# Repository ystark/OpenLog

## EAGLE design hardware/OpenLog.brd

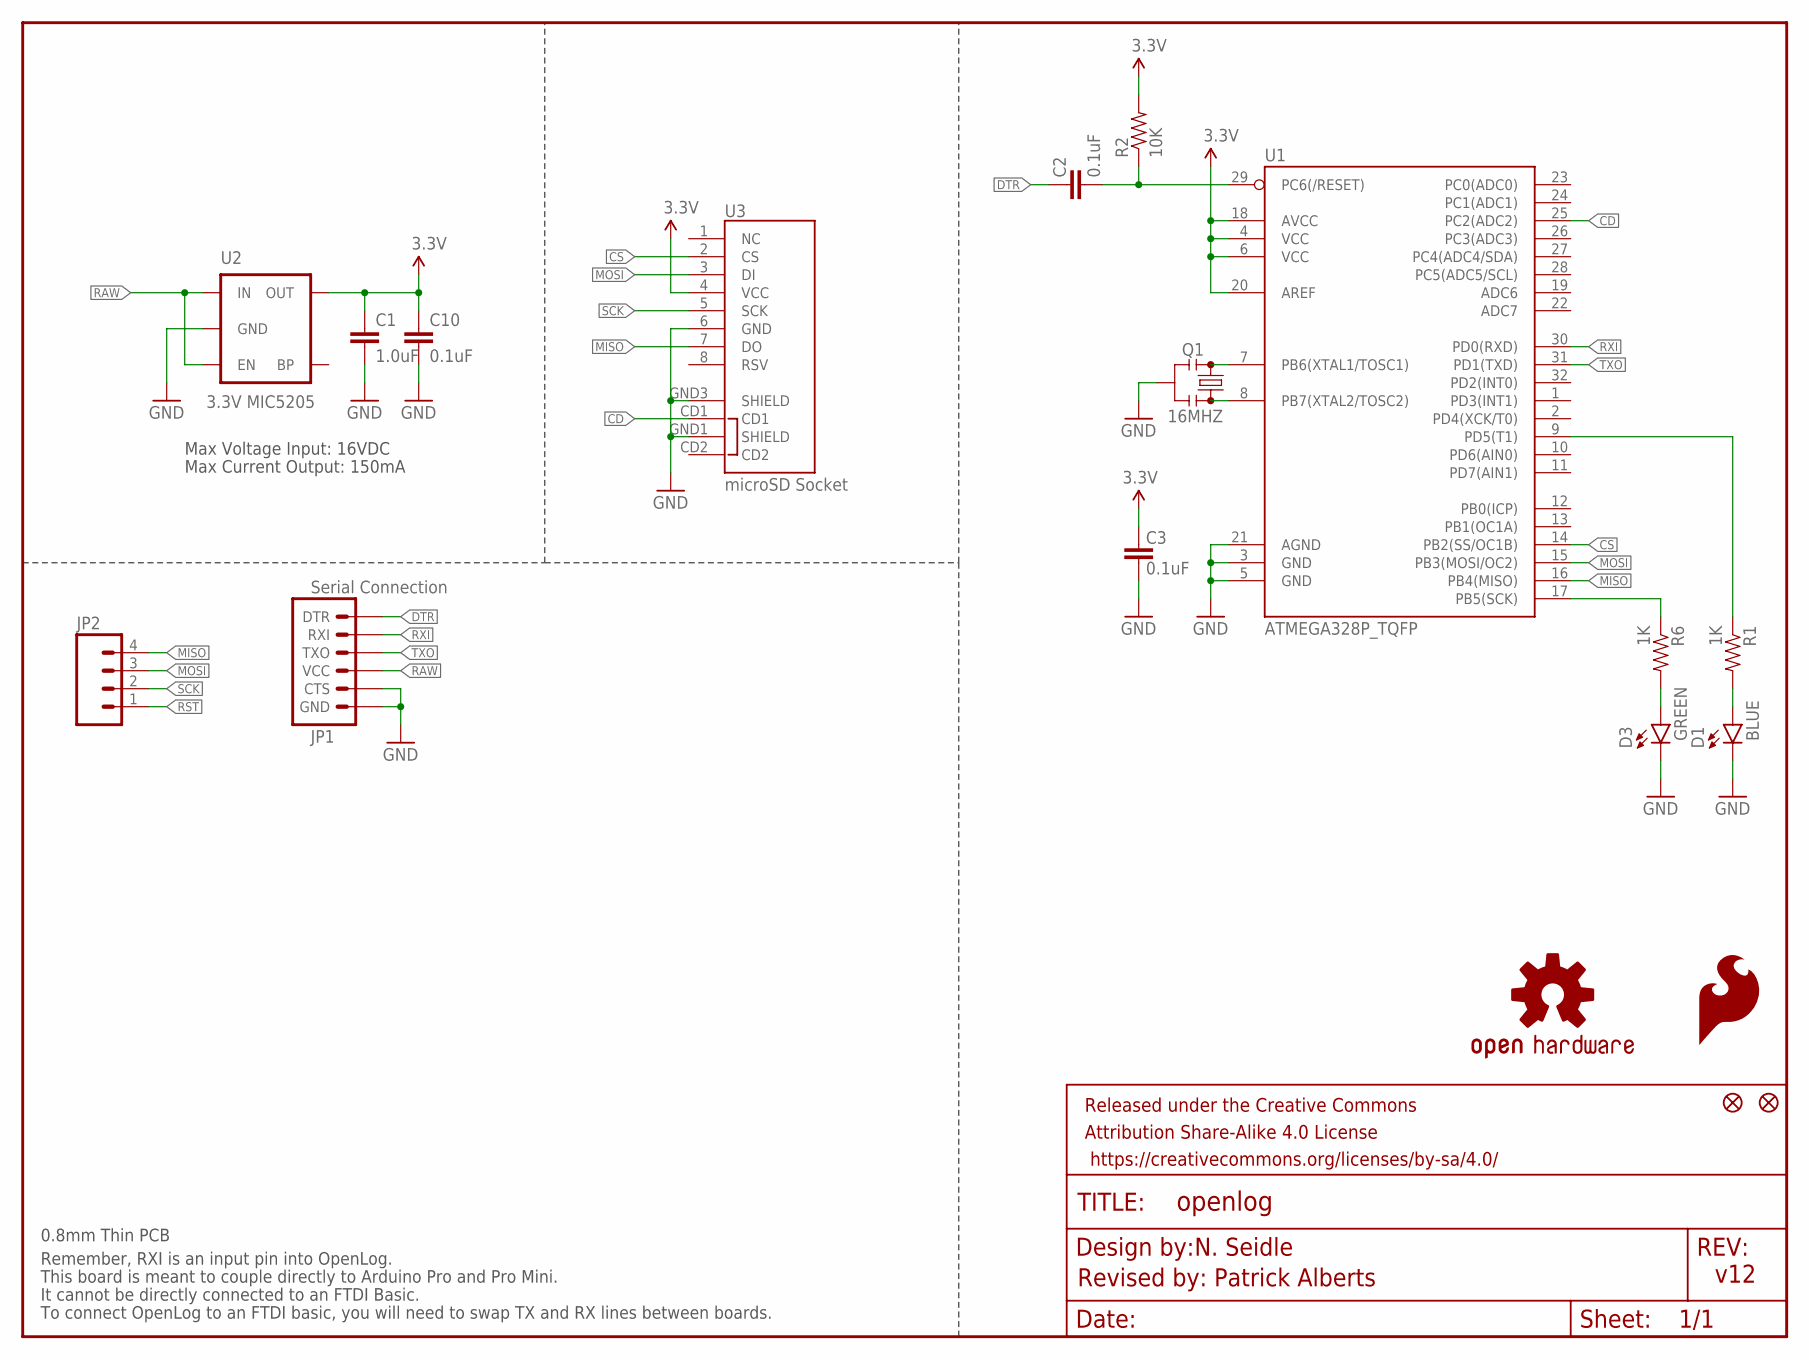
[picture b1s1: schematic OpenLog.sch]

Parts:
C1: 1.0uF; 0603-CAP
C2, C3, C10: 0.1uF; 0603-CAP
D1: BLUE; LED-0603
D3: GREEN; LED-0603
FID1, FID2: FIDUCIALUFIDUCIAL; MICRO-FIDUCIAL
FRAME1: FRAME-LETTER; CREATIVE_COMMONS
JP1: Serial Connection; 1X06
JP2: M04PTH; 1X04
LOGO1: SFE_LOGO_FLAME.1_INCH; SFE_LOGO_FLAME_.1
LOGO2: OSHW-LOGOS; OSHW-LOGO-S
Q1: 16MHZ; RESONATOR-SMD
R1, R6: 1K; 0603-RES
R2: 10K; 0603-RES
U1: ATMEGA328P_TQFP; TQFP32-08
U2: 3.3V MIC5205; SOT23-5
U3: microSD Socket; MICROSD_1:1

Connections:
3.3V: C1.1, C3.2, C10.1, R2.2, U1.4 (VCC), U1.6 (VCC), U1.18 (AVCC), U1.20 (AREF), U2.5 (OUT), U3.4 (VCC)
CD: U1.25 (PC2(ADC2)), U3.CD1
CS: U1.14 (PB2(SS/OC1B)), U3.2 (CS)
DTR: C2.2, JP1.1 (DTR)
GND: C1.2, C3.1, C10.2, D1.C, D3.C, JP1.5 (CTS), JP1.6 (GND), Q1.2, U1.3 (GND), U1.5 (GND), U1.21 (AGND), U2.2 (GND), U3.6 (GND), U3.GND1 (SHIELD), U3.GND3 (SHIELD)
MISO: JP2.4, U1.16 (PB4(MISO)), U3.7 (DO)
MOSI: JP2.3, U1.15 (PB3(MOSI/OC2)), U3.3 (DI)
unnamed: Q1.1, U1.8 (PB7(XTAL2/TOSC2))
unnamed: Q1.3, U1.7 (PB6(XTAL1/TOSC1))
unnamed: D1.A, R1.2
unnamed: R1.1, U1.9 (PD5(T1))
unnamed: D3.A, R6.2
RAW: JP1.4 (VCC), U2.1 (IN), U2.3 (EN)
RST: C2.1, JP2.1, R2.1, U1.29 (PC6(/RESET))
RXI: JP1.2 (RXI), U1.30 (PD0(RXD))
SCK: JP2.2, R6.1, U1.17 (PB5(SCK)), U3.5 (SCK)
TXO: JP1.3 (TXO), U1.31 (PD1(TXD))

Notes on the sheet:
Max Voltage Input: 16VDC
Max Current Output: 150mA
Remember, RXI is an input pin into OpenLog.
This board is meant to couple directly to Arduino Pro and Pro Mini.
It cannot be directly connected to an FTDI Basic.
To connect OpenLog to an FTDI basic, you will need to swap TX and RX lines between boards.
v12
N. Seidle
Revised by: Patrick Alberts
0.8mm Thin PCB

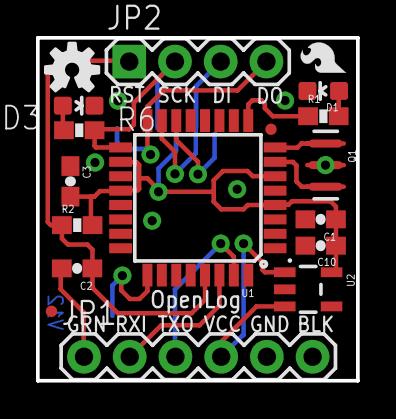
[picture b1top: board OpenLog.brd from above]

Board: 2 copper layers, 17.8 x 19.1 mm, 20 parts (1 on the bottom side), 17 nets.

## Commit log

2010-09-29 v2.21 ringp fork brought in. Wildcard remove and list commands now work. Remove directory now works! Change directory up/down the tree works again.
    28440 bytes used of 30720.
    ringp brought back many great commands! Thanks ringp!
    rm LOG*.* works
    ls *.TXT works
    cd .. works again
    ls now correctly shows directories first and files following the directories.
2010-11-03 Added "rm -rf" command that will remove all contents of the directory including subdirectories recursively. The read-only attribute for files will be ignored.
2010-11-03 Added .gitignore to ignore *.class and *.jpf files.
2015-05-05 Rev Changes made
    Updated to current standards
    0603
    Sch
    switched micro sd socket
2015-05-06 Moved Silk
2015-05-07 Initial QC checklist run though
    As in my own, before I actually get one done.
2015-05-07 Added OSHW Logo
2015-05-07 Fixed Version #
2015-05-08 FIxed QC issues
2015-05-08 Fixed QC issues

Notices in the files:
parts and their libraries:
SparkFun-Connectors: Licensing: Creative Commons ShareAlike 4.0 International - https://creativecommons.org/licenses/by-sa/4.0
SparkFun-Aesthetics: Released under the Creative Commons Attribution Share-Alike 4.0 License
SparkFun-Aesthetics: https://creativecommons.org/licenses/by-sa/4.0
